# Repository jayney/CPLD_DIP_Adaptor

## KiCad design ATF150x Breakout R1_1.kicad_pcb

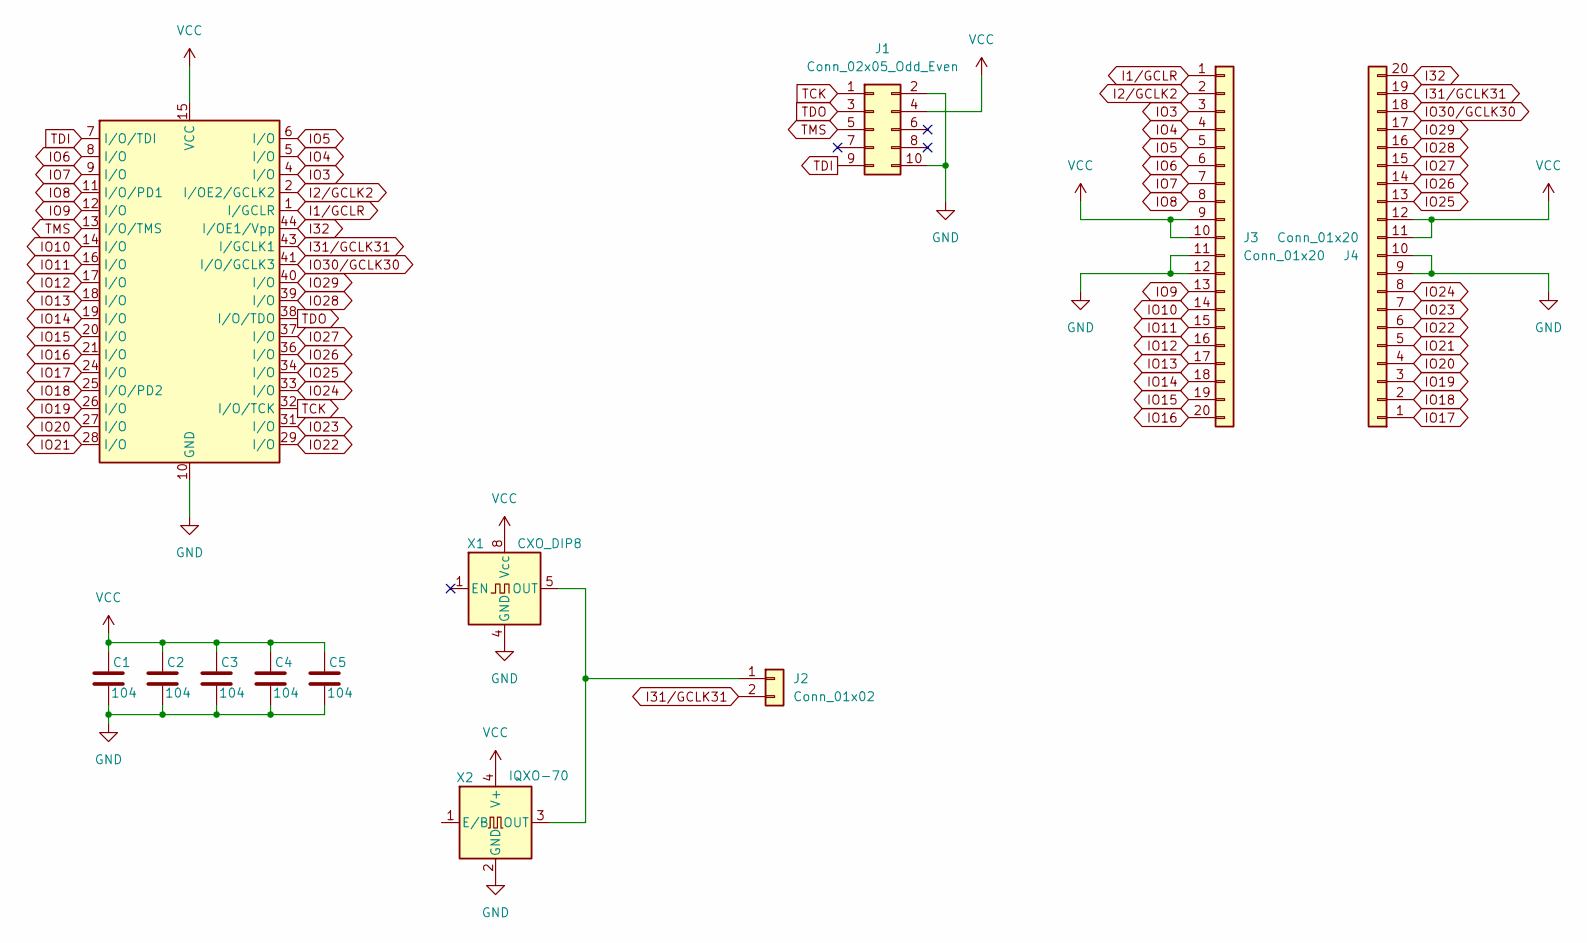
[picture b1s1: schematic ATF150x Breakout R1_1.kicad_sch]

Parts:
C1, C2, C3, C4, C5: 104; C_0805_2012Metric_Pad1.18x1.45mm_HandSolder; LCSC C14663
J1: Conn_02x05_Odd_Even; PinHeader_2x05_P2.54mm_Vertical
J2: Conn_01x02; PinHeader_1x02_P2.54mm_Vertical
J3, J4: Conn_01x20; PinHeader_1x20_P2.54mm_Vertical
U1: ATF1502AS-Jx44; PLCC-44_THT-Socket
X1: CXO_DIP8; Oscillator_DIP-8
X2: IQXO-70; Oscillator_SMD_EuroQuartz_XO53-4Pin_5.0x3.2mm

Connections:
GND: C1.2, C2.2, C3.2, C4.2, C5.2, J1.2, J1.10, J3.11, J3.12, J4.9, J4.10, U1.10 (GND), U1.22 (GND), U1.30 (GND), U1.42 (GND), X1.4 (GND), X2.2 (GND)
I1/GCLR: J3.1, U1.1 (I/GCLR)
I2/GCLK2: J3.2, U1.2 (I/OE2/GCLK2)
I31/GCLK31: J2.2, J4.19, U1.43 (I/GCLK1)
I32: J4.20, U1.44 (I/OE1/Vpp)
IO3: J3.3, U1.4 (I/O)
IO4: J3.4, U1.5 (I/O)
IO5: J3.5, U1.6 (I/O)
IO6: J3.6, U1.8 (I/O)
IO7: J3.7, U1.9 (I/O)
IO8: J3.8, U1.11 (I/O/PD1)
IO9: J3.13, U1.12 (I/O)
IO10: J3.14, U1.14 (I/O)
IO11: J3.15, U1.16 (I/O)
IO12: J3.16, U1.17 (I/O)
IO13: J3.17, U1.18 (I/O)
IO14: J3.18, U1.19 (I/O)
IO15: J3.19, U1.20 (I/O)
IO16: J3.20, U1.21 (I/O)
IO17: J4.1, U1.24 (I/O)
IO18: J4.2, U1.25 (I/O/PD2)
IO19: J4.3, U1.26 (I/O)
IO20: J4.4, U1.27 (I/O)
IO21: J4.5, U1.28 (I/O)
IO22: J4.6, U1.29 (I/O)
IO23: J4.7, U1.31 (I/O)
IO24: J4.8, U1.33 (I/O)
IO25: J4.13, U1.34 (I/O)
IO26: J4.14, U1.36 (I/O)
IO27: J4.15, U1.37 (I/O)
IO28: J4.16, U1.39 (I/O)
IO29: J4.17, U1.40 (I/O)
IO30/GCLK30: J4.18, U1.41 (I/O/GCLK3)
unnamed: J2.1, X1.5 (OUT), X2.3 (OUT)
TCK: J1.1, U1.32 (I/O/TCK)
TDI: J1.9, U1.7 (I/O/TDI)
TDO: J1.3, U1.38 (I/O/TDO)
TMS: J1.5, U1.13 (I/O/TMS)
VCC: C1.1, C2.1, C3.1, C4.1, C5.1, J1.4, J3.9, J3.10, J4.11, J4.12, U1.3 (VCC), U1.15 (VCC), U1.23 (VCC), U1.35 (VCC), X1.8 (Vcc), X2.4 (V+)

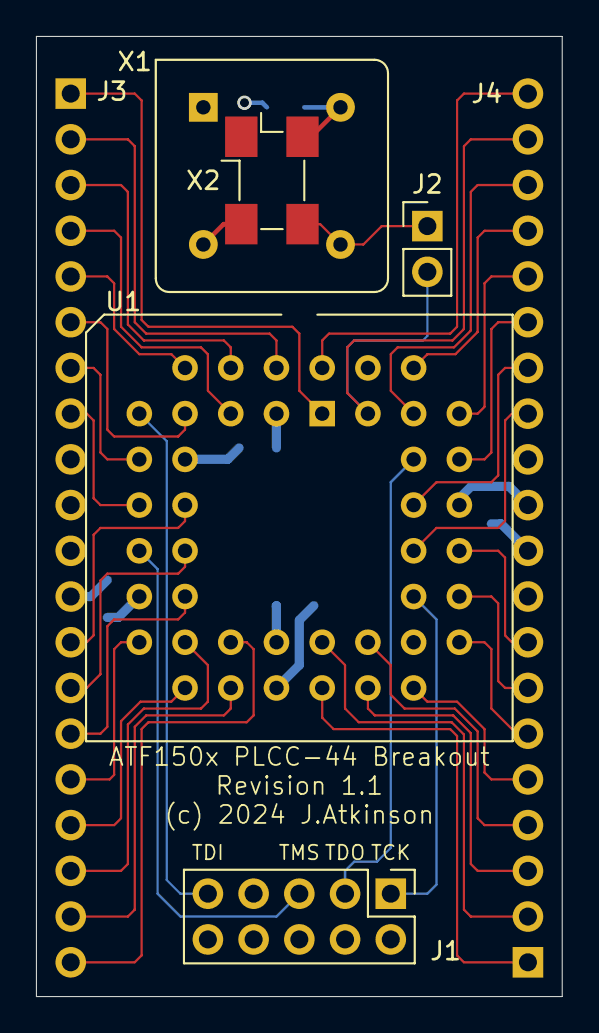
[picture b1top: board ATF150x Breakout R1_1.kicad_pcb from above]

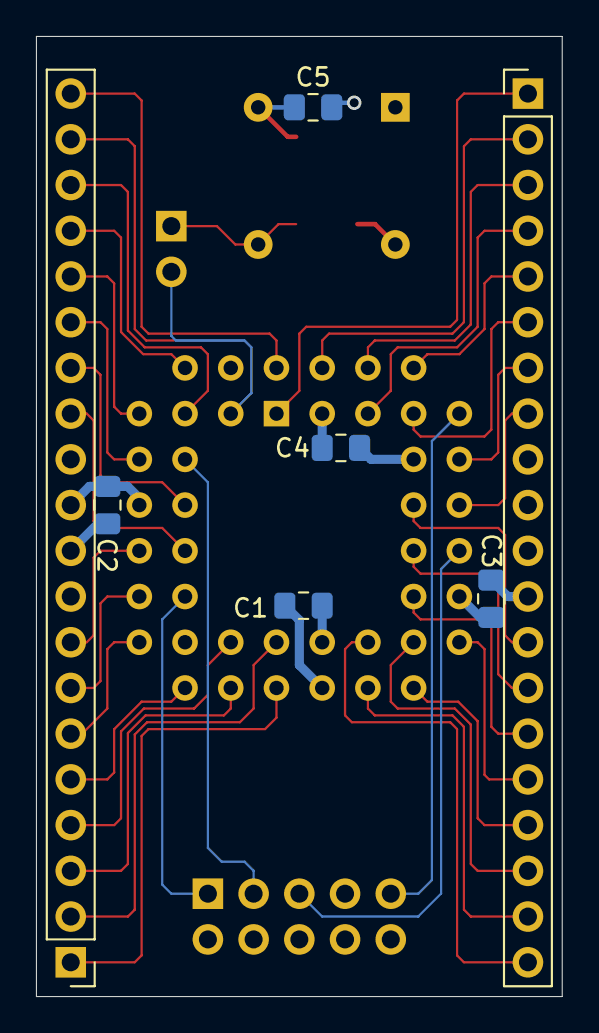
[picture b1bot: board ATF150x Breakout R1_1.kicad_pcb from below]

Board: 4 copper layers, 29.2 x 53.3 mm, 12 parts (7 on the bottom side), 39 nets.

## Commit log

2024-11-18 Initial Commit
    Created in Kicad 8.
    Board is compatible with ATF1502 & ATF1504 CPLD's - QFP44 only.
    JTAG header is included, compatible with Microchips ATDH1150 programmer. Footprints for DIP8 & SMD oscillators are included, along with jumper to connect to CPLD

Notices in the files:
ATF150x Breakout R1_1.kicad_pcb:
(c) 2024 J.Atkinson
